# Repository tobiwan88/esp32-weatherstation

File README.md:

# esp32-weatherstation

Outdoor air-quality and weather stations for my own use (Munich): PM1 / PM2.5 / PM10, temperature, humidity and pressure, with an
optional ozone module, reported over WiFi to Home Assistant (MQTT). The AQI and trends are computed on the Home Assistant side.
Solar powered with optional USB, ESP32-S3, deep-sleep duty cycle (every 30 min; every 15 min only while USB or strong sun is
present). Custom PCBs assembled by JLCPCB. Some sites are sheltered with USB nearby, some are exposed on a roof or pole on solar
only; the design target is the exposed case.

**Status (2026-11-23):** the hardware is three boards plus bought parts. The power board and the main board have schematics,
placement and routing done and pass their checks (KiCad DRC clean, EMI rows OK); there are no fab files yet and nothing is ordered.
The sensor head board exists as an SHT45 design; the switch to the cheaper SHT40 decided in the requirements is not done yet.
Firmware is not started. Board by board: `hardware/README.md`.

## The system
| Part | What |
|---|---|
| Power board | BQ25798 charger fed from the solar panel (hardware MPPT) and USB, one 1S LiFePO4 26700 cell with protection IC, panel TVS and choke, cell fuse and NTC. 4 layers, at most 50 x 50 mm. No 3.3 V rail on this board |
| Main board | ESP32-S3-WROOM-1 module, USB-C (programming, debug, VBUS to the power board), 3.3 V buck-boost, switched 3V3_SW and 5V_SW rails, BMP580 pressure sensor, sensor ports (2 x Qwiic, 2.54 mm I2C header, 5 V UART, ozone module, rain/wind pulse port). 4 layers, at most 50 x 50 mm |
| Sensor head | temperature and humidity (Sensirion SHT4x) on its own small 2-layer board in a radiation shield, joined by a Qwiic cable |
| Bought | 5 W 6 V solar panel, LiFePO4 cell, PM sensor (DFRobot SEN0460 on I2C, or Plantower PMS7003 on UART), optional rain gauge, anemometer, ozone and UV modules, enclosure |
The power and main boards are joined by a keyed 2 x 10 header (J10: SYS, USB VBUS and D+/D-, charger I2C and interrupt, charge enable). A bought charger
module that supplies SYS can replace the power board. Contract and pin table: `hardware/ARCHITECTURE.md`.

## Numbers that drive the design
| | Value | Source |
|---|---|---|
| Budget | each JLCPCB assembly order under USD 100, whole project under USD 500 | `hardware/REQUIREMENTS-system.md` section 2 |
| Parts plus fees per order, 5 boards (before bare PCB, SMT joints, shipping) | power board USD 55.02, main board USD 88.91 (live stock and first price tier, 2026-11-24) | `hardware/calc/bom_check.py hardware/<board> --stock --qty 5` |
| Average current, 30 min cycle | 11.8 mA, 0.90 Wh/day | `hardware/calc/power_budget.py hardware/power-board` |
| Autonomy without sun | 11.1 days (at least 7 required) | same |
| Worst-month solar margin | 2.33 x (want 1.5 x) | same |
| Sleep current of the whole stack | 75 uA typical, 85 uA with datasheet maxima (target under 100 uA) | same |
The 15 min cycle draws 22 mA and gives 5.9 days, so it is allowed only with an external energy source. A real JLCPCB quote per
order is still needed: there is no scriptable quote.

## Where to look
- `hardware/README.md`: boards, status, and the map of the hardware tree. `hardware/PLAN.md`: what is done and what comes next.
- `hardware/REQUIREMENTS-system.md`, `hardware/ARCHITECTURE.md`, `hardware/DECISIONS.md`: requirements, how the boards fit, decisions.
- `hardware/GATES.md`: where each board stands in the six design gates.
- `firmware/`: ESP-IDF project (not started); the rules the hardware depends on are in `hardware/FIRMWARE-RULES.md`.
- `hw-kit/`: the reusable hardware kit (skills, agents, check scripts, templates) this project is built with; `CLAUDE.md`: agent notes.
- `scripts/check.sh`: the local gate (hardware checks, tests, privacy scan).

Built with the hardware kit in `hw-kit/`, which grew out of [desk_notifier](https://github.com/tobiwan88/desk_notifier). MIT license.

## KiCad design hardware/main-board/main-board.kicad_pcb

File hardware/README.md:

# Hardware: where to look

Boards (one folder each, profile in `board.yaml`, notes in `BOARD.md`). Gate output: `scripts/hw-check.sh`.

| Board | Role | State (details in its `BOARD.md`) |
|---|---|---|
| `power-board/` | charger, protection, solar and USB inputs, header to the main board | routed 2026-11-22, DRC 0 at all severities; no fab files yet |
| `main-board/` | MCU, 3.3 V and 5 V rails, USB-C, sensor ports | routed 2026-11-22, DRC clean (waived silk warnings listed there), EMI check OK; no fab files yet |
| `sht45-board/` | outdoor temperature and humidity head, Qwiic chain-out | layout done 2026-11-04: ERC 0, DRC 0 incl. warnings, parity clean |
| `bmp585-board/`, `veml6030-board/` | pressure and light add-ons on the same base | retired as ordered designs 2026-11-21; DRC clean, parity clean (2026-11-04) |
| `weatherstation-v1/` | first single-board design, kept as history: parts cards and datasheets (its fab files are local and gitignored) | superseded by the split |

| What | Where |
|---|---|
| System requirements, architecture, decisions that must not be lost | `REQUIREMENTS-system.md`, `ARCHITECTURE.md`, `DECISIONS.md` |
| Plan, review rounds, order notes | `PLAN.md`, `REVIEW-*.md`, `ORDER-sensor-boards.md`, `<board>/ORDER.md` |
| Board profile files read by the scripts | `<board>/board.yaml`, `critical.yaml`, `emi.yaml`, `parts/` |
| Board-neutral checks, tools, fab rules | `calc/`, `tools/`, `rules/` (installed from `../hw-kit/tooling`) |
| Generators and project build scripts | `gen/`, `tools/build_*.sh`, `tools/route_*.sh` |
| Skills and agents | `../.claude/` (installed from `../hw-kit`; read `hw-base` first) |
| Earlier project's pipeline to copy from | `reference/desk_notifier/` |

New board: `scripts/new-board.sh <name>`. The kit and how to reuse it in another project: `../hw-kit/README.md`.

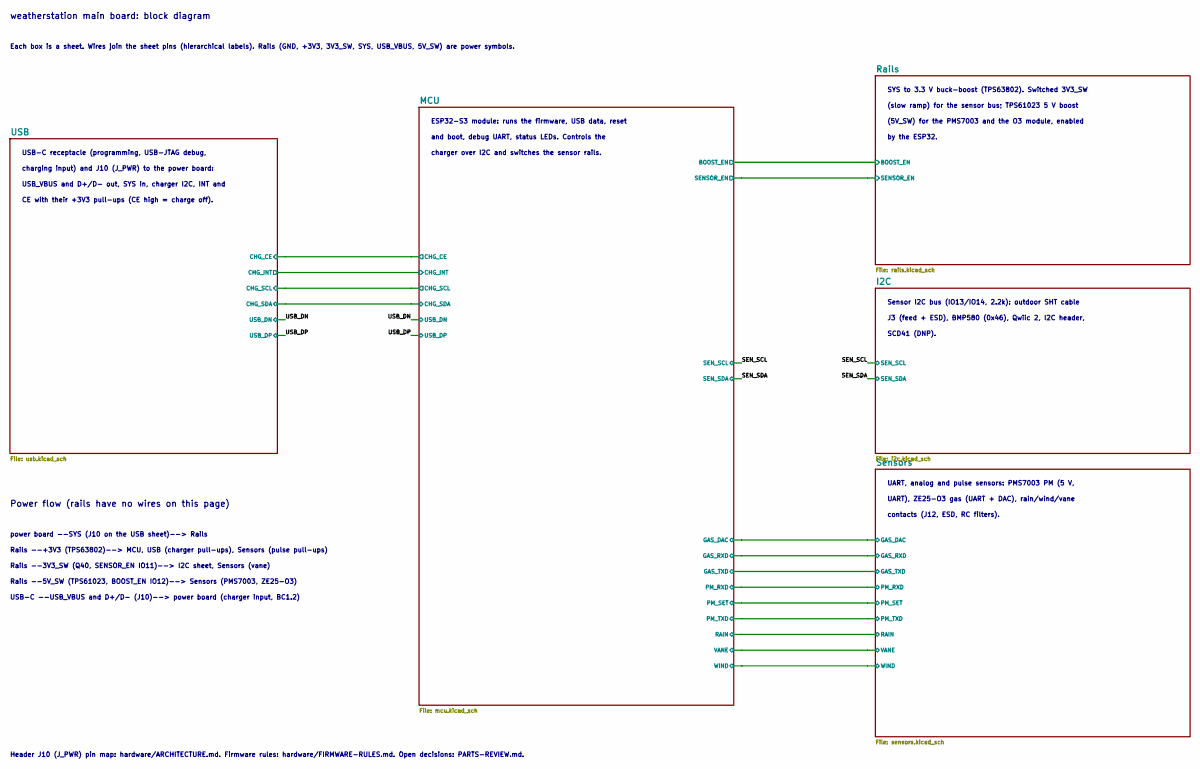
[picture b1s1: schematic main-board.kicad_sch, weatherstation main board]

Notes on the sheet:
weatherstation main board: block diagram
Each box is a sheet. Wires join the sheet pins (hierarchical labels). Rails (GND, +3V3, 3V3_SW, SYS, USB_VBUS, 5V_SW) are power symbols.
Power flow (rails have no wires on this page)
power board --SYS (J10 on the USB sheet)--> Rails
Rails --+3V3 (TPS63802)--> MCU, USB (charger pull-ups), Sensors (pulse pull-ups)
Rails --3V3_SW (Q40, SENSOR_EN IO11)--> I2C sheet, Sensors (vane)
Rails --5V_SW (TPS61023, BOOST_EN IO12)--> Sensors (PMS7003, ZE25-O3)
USB-C --USB_VBUS and D+/D- (J10)--> power board (charger input, BC1.2)
Header J10 (J_PWR) pin map: hardware/ARCHITECTURE.md. Firmware rules: hardware/FIRMWARE-RULES.md. Open decisions: PARTS-REVIEW.md.
USB-C receptacle (programming, USB-JTAG debug,
charging input) and J10 (J_PWR) to the power board:
USB_VBUS and D+/D- out, SYS in, charger I2C, INT and
CE with their +3V3 pull-ups (CE high = charge off).
ESP32-S3 module: runs the firmware, USB data, reset
and boot, debug UART, status LEDs. Controls the
charger over I2C and switches the sensor rails.
SYS to 3.3 V buck-boost (TPS63802). Switched 3V3_SW
(slow ramp) for the sensor bus; TPS61023 5 V boost
(5V_SW) for the PMS7003 and the O3 module, enabled
by the ESP32.
Sensor I2C bus (IO13/IO14, 2.2k): outdoor SHT cable
J3 (feed + ESD), BMP580 (0x46), Qwiic 2, I2C header,
SCD41 (DNP).
UART, analog and pulse sensors: PMS7003 PM (5 V,
UART), ZE25-O3 gas (UART + DAC), rain/wind/vane
contacts (J12, ESD, RC filters).

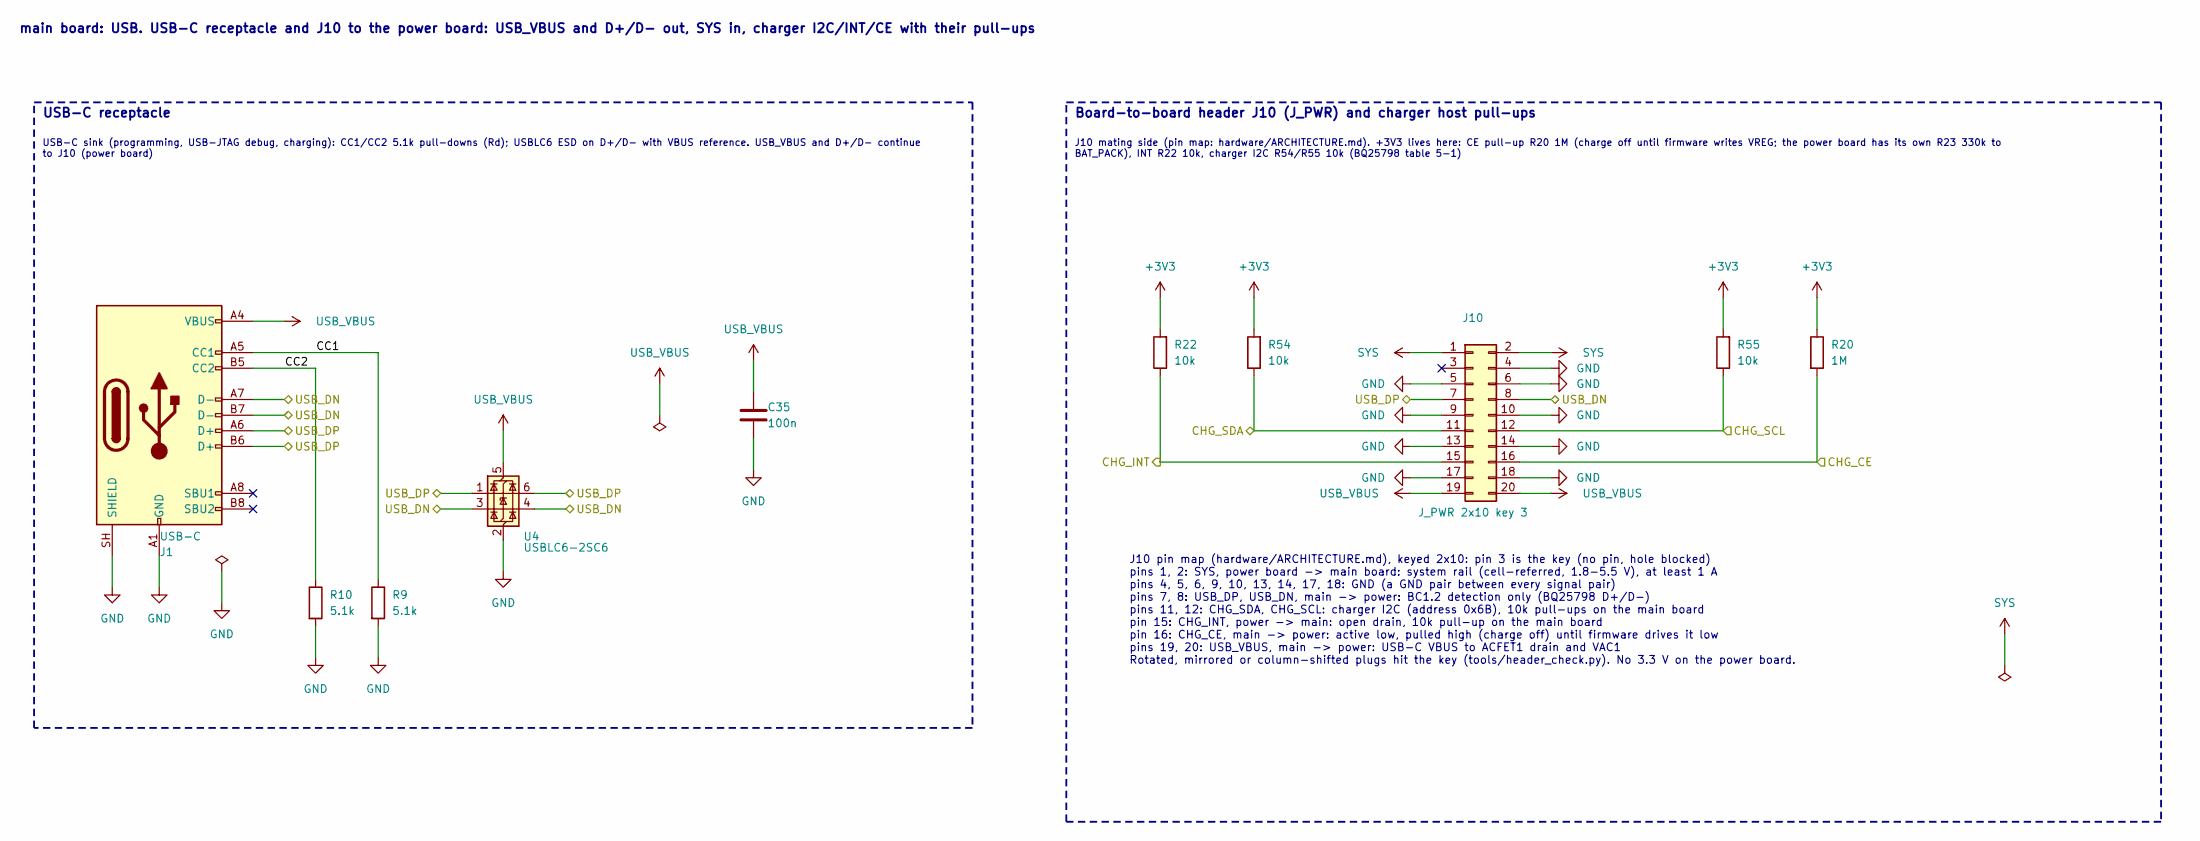
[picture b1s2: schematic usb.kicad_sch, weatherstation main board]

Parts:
C35: 100n; C_0402_1005Metric; LCSC C307331
J1: USB-C; USB_C_Receptacle_HRO_TYPE-C-31-M-12; LCSC C165948
J10: J_PWR 2x10 key 3; PinHeader_2x10_P2.54mm_Vertical
R9, R10: 5.1k; R_0402_1005Metric; LCSC C25905
R20: 1M; R_0402_1005Metric; LCSC C26083
R22, R54, R55: 10k; R_0402_1005Metric; LCSC C25744
U4: USBLC6-2SC6; SOT-23-6; LCSC C7519

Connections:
+3V3: R20.1, R22.2, R54.2, R55.2; also elsewhere on the board
/MCU/CHG_CE: J10.16, R20.2; also elsewhere on the board
/MCU/CHG_INT: J10.15, R22.1; also elsewhere on the board
/MCU/CHG_SCL: J10.12, R55.1; also elsewhere on the board
/MCU/CHG_SDA: J10.11, R54.1; also elsewhere on the board
/USB/CC1: J1.A5 (CC1), R9.1
/USB/CC2: J1.B5 (CC2), R10.1
/USB_DN: J1.A7 (D-), J1.B7 (D-), J10.8, U4.3 (I/O2), U4.4 (I/O2); also elsewhere on the board
/USB_DP: J1.A6 (D+), J1.B6 (D+), J10.7, U4.1 (I/O1), U4.6 (I/O1); also elsewhere on the board
GND: C35.2, J1.A1 (GND), J1.A12 (GND), J1.B1 (GND), J1.B12 (GND), J1.SH (SHIELD), J10.4, J10.5, J10.6, J10.9, J10.10, J10.13, J10.14, J10.17, J10.18, R9.2, R10.2, U4.2 (GND); also elsewhere on the board
SYS: J10.1, J10.2; also elsewhere on the board
USB_VBUS: C35.1, J1.A4 (VBUS), J1.A9 (VBUS), J1.B4 (VBUS), J1.B9 (VBUS), J10.19, J10.20, U4.5 (VBUS)

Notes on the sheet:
USB-C receptacle
USB-C sink (programming, USB-JTAG debug, charging): CC1/CC2 5.1k pull-downs (Rd); USBLC6 ESD on D+/D- with VBUS reference. USB_VBUS and D+/D- continue to J10 (power board)
Board-to-board header J10 (J_PWR) and charger host pull-ups
J10 mating side (pin map: hardware/ARCHITECTURE.md). +3V3 lives here: CE pull-up R20 1M (charge off until firmware writes VREG; the power board has its own R23 330k to BAT_PACK), INT R22 10k, charger I2C R54/R55 10k (BQ25798 table 5-1)
J10 pin map (hardware/ARCHITECTURE.md), keyed 2x10: pin 3 is the key (no pin, hole blocked) pins 1, 2: SYS, power board -> main board: system rail (cell-referred, 1.8-5.5 V), at least 1 A pins 4, 5, 6, 9, 10, 13, 14, 17, 18: GND (a GND pair between every signal pair) pins 7, 8: USB_DP, USB_DN, main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
main board: USB. USB-C receptacle and J10 to the power board: USB_VBUS and D+/D- out, SYS in, charger I2C/INT/CE with their pull-ups

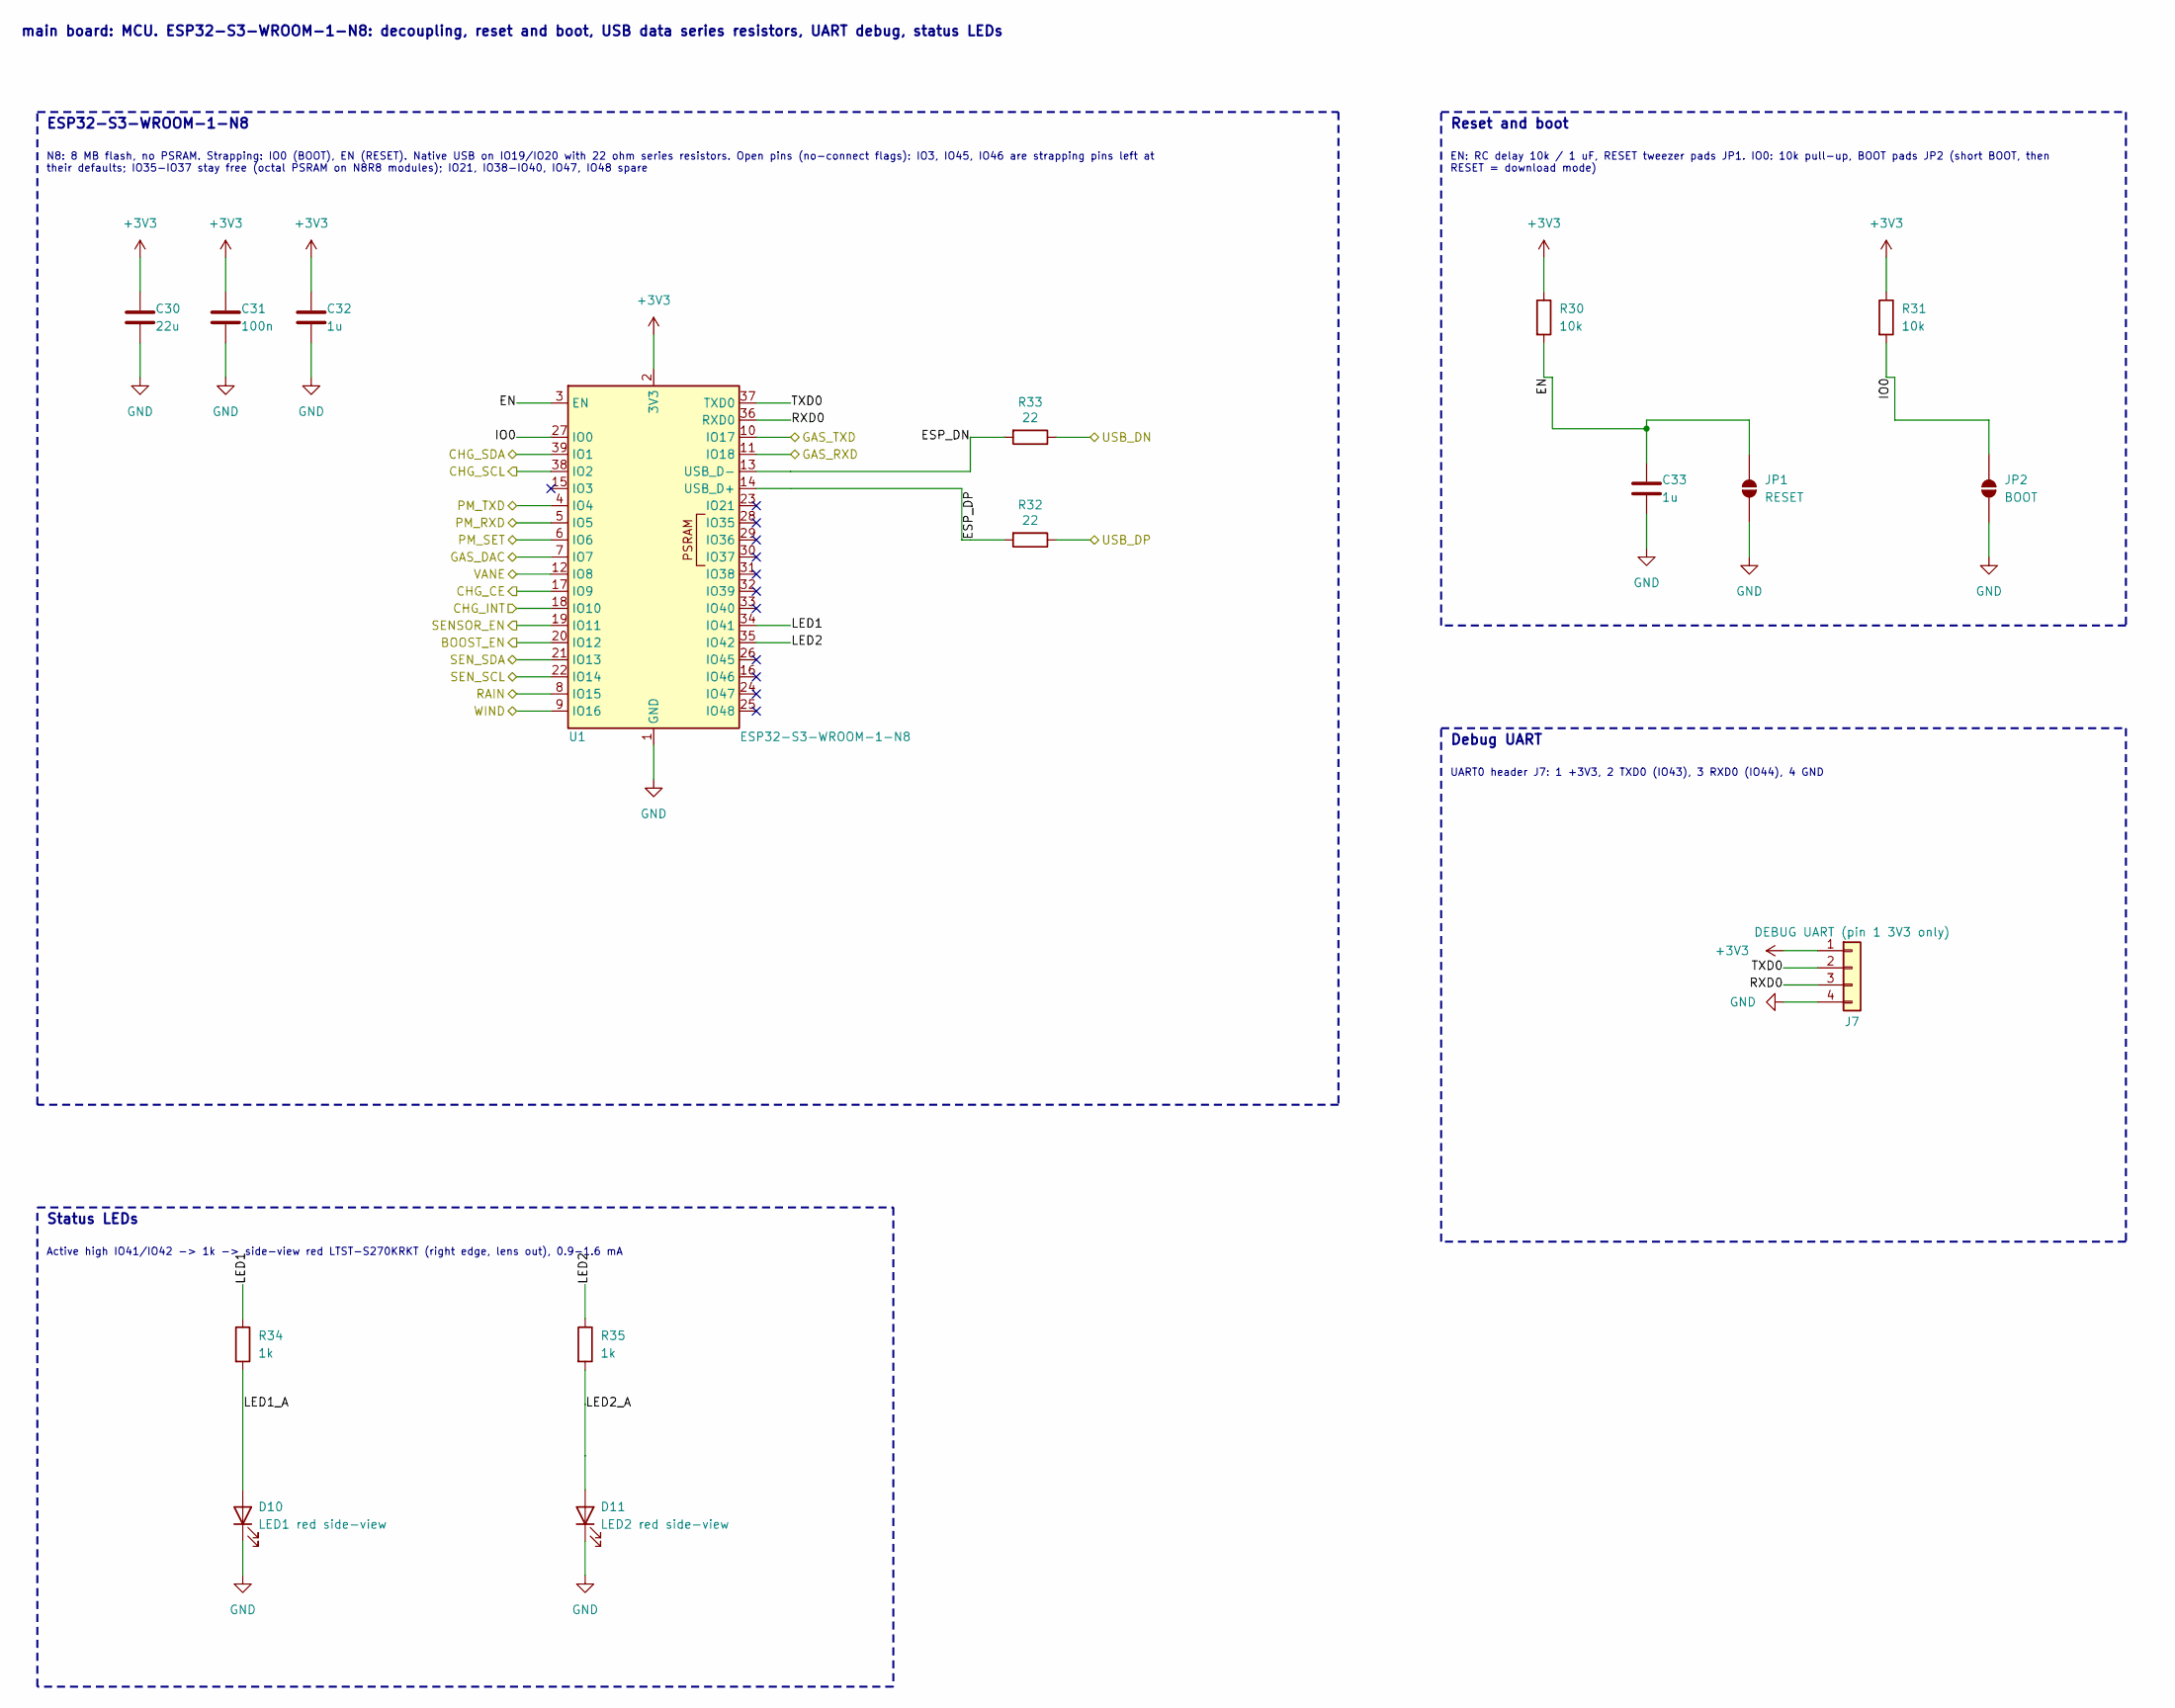
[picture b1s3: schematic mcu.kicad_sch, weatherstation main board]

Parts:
C30: 22u; C_0805_2012Metric; LCSC C45783
C31: 100n; C_0402_1005Metric; LCSC C307331
C32, C33: 1u; C_0402_1005Metric; LCSC C52923
D10: LED1 red side-view; LED_LiteOn_LTST-S270_SideView; LCSC C125114
D11: LED2 red side-view; LED_LiteOn_LTST-S270_SideView; LCSC C125114
J7: DEBUG UART (pin 1 3V3 only); PinHeader_1x04_P2.54mm_Vertical
JP1: RESET; SolderJumper-2_P1.3mm_Open_RoundedPad1.0x1.5mm
JP2: BOOT; SolderJumper-2_P1.3mm_Open_RoundedPad1.0x1.5mm
R30, R31: 10k; R_0402_1005Metric; LCSC C25744
R32, R33: 22; R_0402_1005Metric; LCSC C25092
R34, R35: 1k; R_0402_1005Metric; LCSC C11702
U1: ESP32-S3-WROOM-1-N8; ESP32-S3-WROOM-1; LCSC C2913198

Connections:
+3V3: C30.1, C31.1, C32.1, J7.1, R30.1, R31.1, U1.2 (3V3); also elsewhere on the board
/MCU/BOOST_EN: U1.20 (IO12); also elsewhere on the board
/MCU/CHG_CE: U1.17 (IO9); also elsewhere on the board
/MCU/CHG_INT: U1.18 (IO10); also elsewhere on the board
/MCU/CHG_SCL: U1.38 (IO2); also elsewhere on the board
/MCU/CHG_SDA: U1.39 (IO1); also elsewhere on the board
/MCU/EN: C33.1, JP1.1 (A), R30.2, U1.3 (EN)
/MCU/ESP_DN: R33.2, U1.13 (USB_D-)
/MCU/ESP_DP: R32.2, U1.14 (USB_D+)
/MCU/GAS_DAC: U1.7 (IO7); also elsewhere on the board
/MCU/GAS_RXD: U1.11 (IO18); also elsewhere on the board
/MCU/GAS_TXD: U1.10 (IO17); also elsewhere on the board
/MCU/IO0: JP2.1 (A), R31.2, U1.27 (IO0)
/MCU/LED1: R34.1, U1.34 (IO41)
/MCU/LED1_A: D10.2 (A), R34.2
/MCU/LED2: R35.1, U1.35 (IO42)
/MCU/LED2_A: D11.2 (A), R35.2
/MCU/PM_RXD: U1.5 (IO5); also elsewhere on the board
/MCU/PM_SET: U1.6 (IO6); also elsewhere on the board
/MCU/PM_TXD: U1.4 (IO4); also elsewhere on the board
/MCU/RAIN: U1.8 (IO15); also elsewhere on the board
/MCU/RXD0: J7.3, U1.36 (RXD0)
/MCU/SENSOR_EN: U1.19 (IO11); also elsewhere on the board
/MCU/TXD0: J7.2, U1.37 (TXD0)
/MCU/VANE: U1.12 (IO8); also elsewhere on the board
/MCU/WIND: U1.9 (IO16); also elsewhere on the board
/SEN_SCL: U1.22 (IO14); also elsewhere on the board
/SEN_SDA: U1.21 (IO13); also elsewhere on the board
/USB_DN: R33.1; also elsewhere on the board
/USB_DP: R32.1; also elsewhere on the board
GND: C30.2, C31.2, C32.2, C33.2, D10.1 (K), D11.1 (K), J7.4, JP1.2 (B), JP2.2 (B), U1.1 (GND), U1.40 (GND), U1.41 (GND); also elsewhere on the board

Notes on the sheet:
ESP32-S3-WROOM-1-N8
N8: 8 MB flash, no PSRAM. Strapping: IO0 (BOOT), EN (RESET). Native USB on IO19/IO20 with 22 ohm series resistors. Open pins (no-connect flags): IO3, IO45, IO46 are strapping pins left at their defaults; IO35-IO37 stay free (octal PSRAM on N8R8 modules); IO21, IO38-IO40, IO47, IO48 spare
Reset and boot
EN: RC delay 10k / 1 uF, RESET tweezer pads JP1. IO0: 10k pull-up, BOOT pads JP2 (short BOOT, then RESET = download mode)
Debug UART
UART0 header J7: 1 +3V3, 2 TXD0 (IO43), 3 RXD0 (IO44), 4 GND
Status LEDs
Active high IO41/IO42 -> 1k -> side-view red LTST-S270KRKT (right edge, lens out), 0.9-1.6 mA
main board: MCU. ESP32-S3-WROOM-1-N8: decoupling, reset and boot, USB data series resistors, UART debug, status LEDs

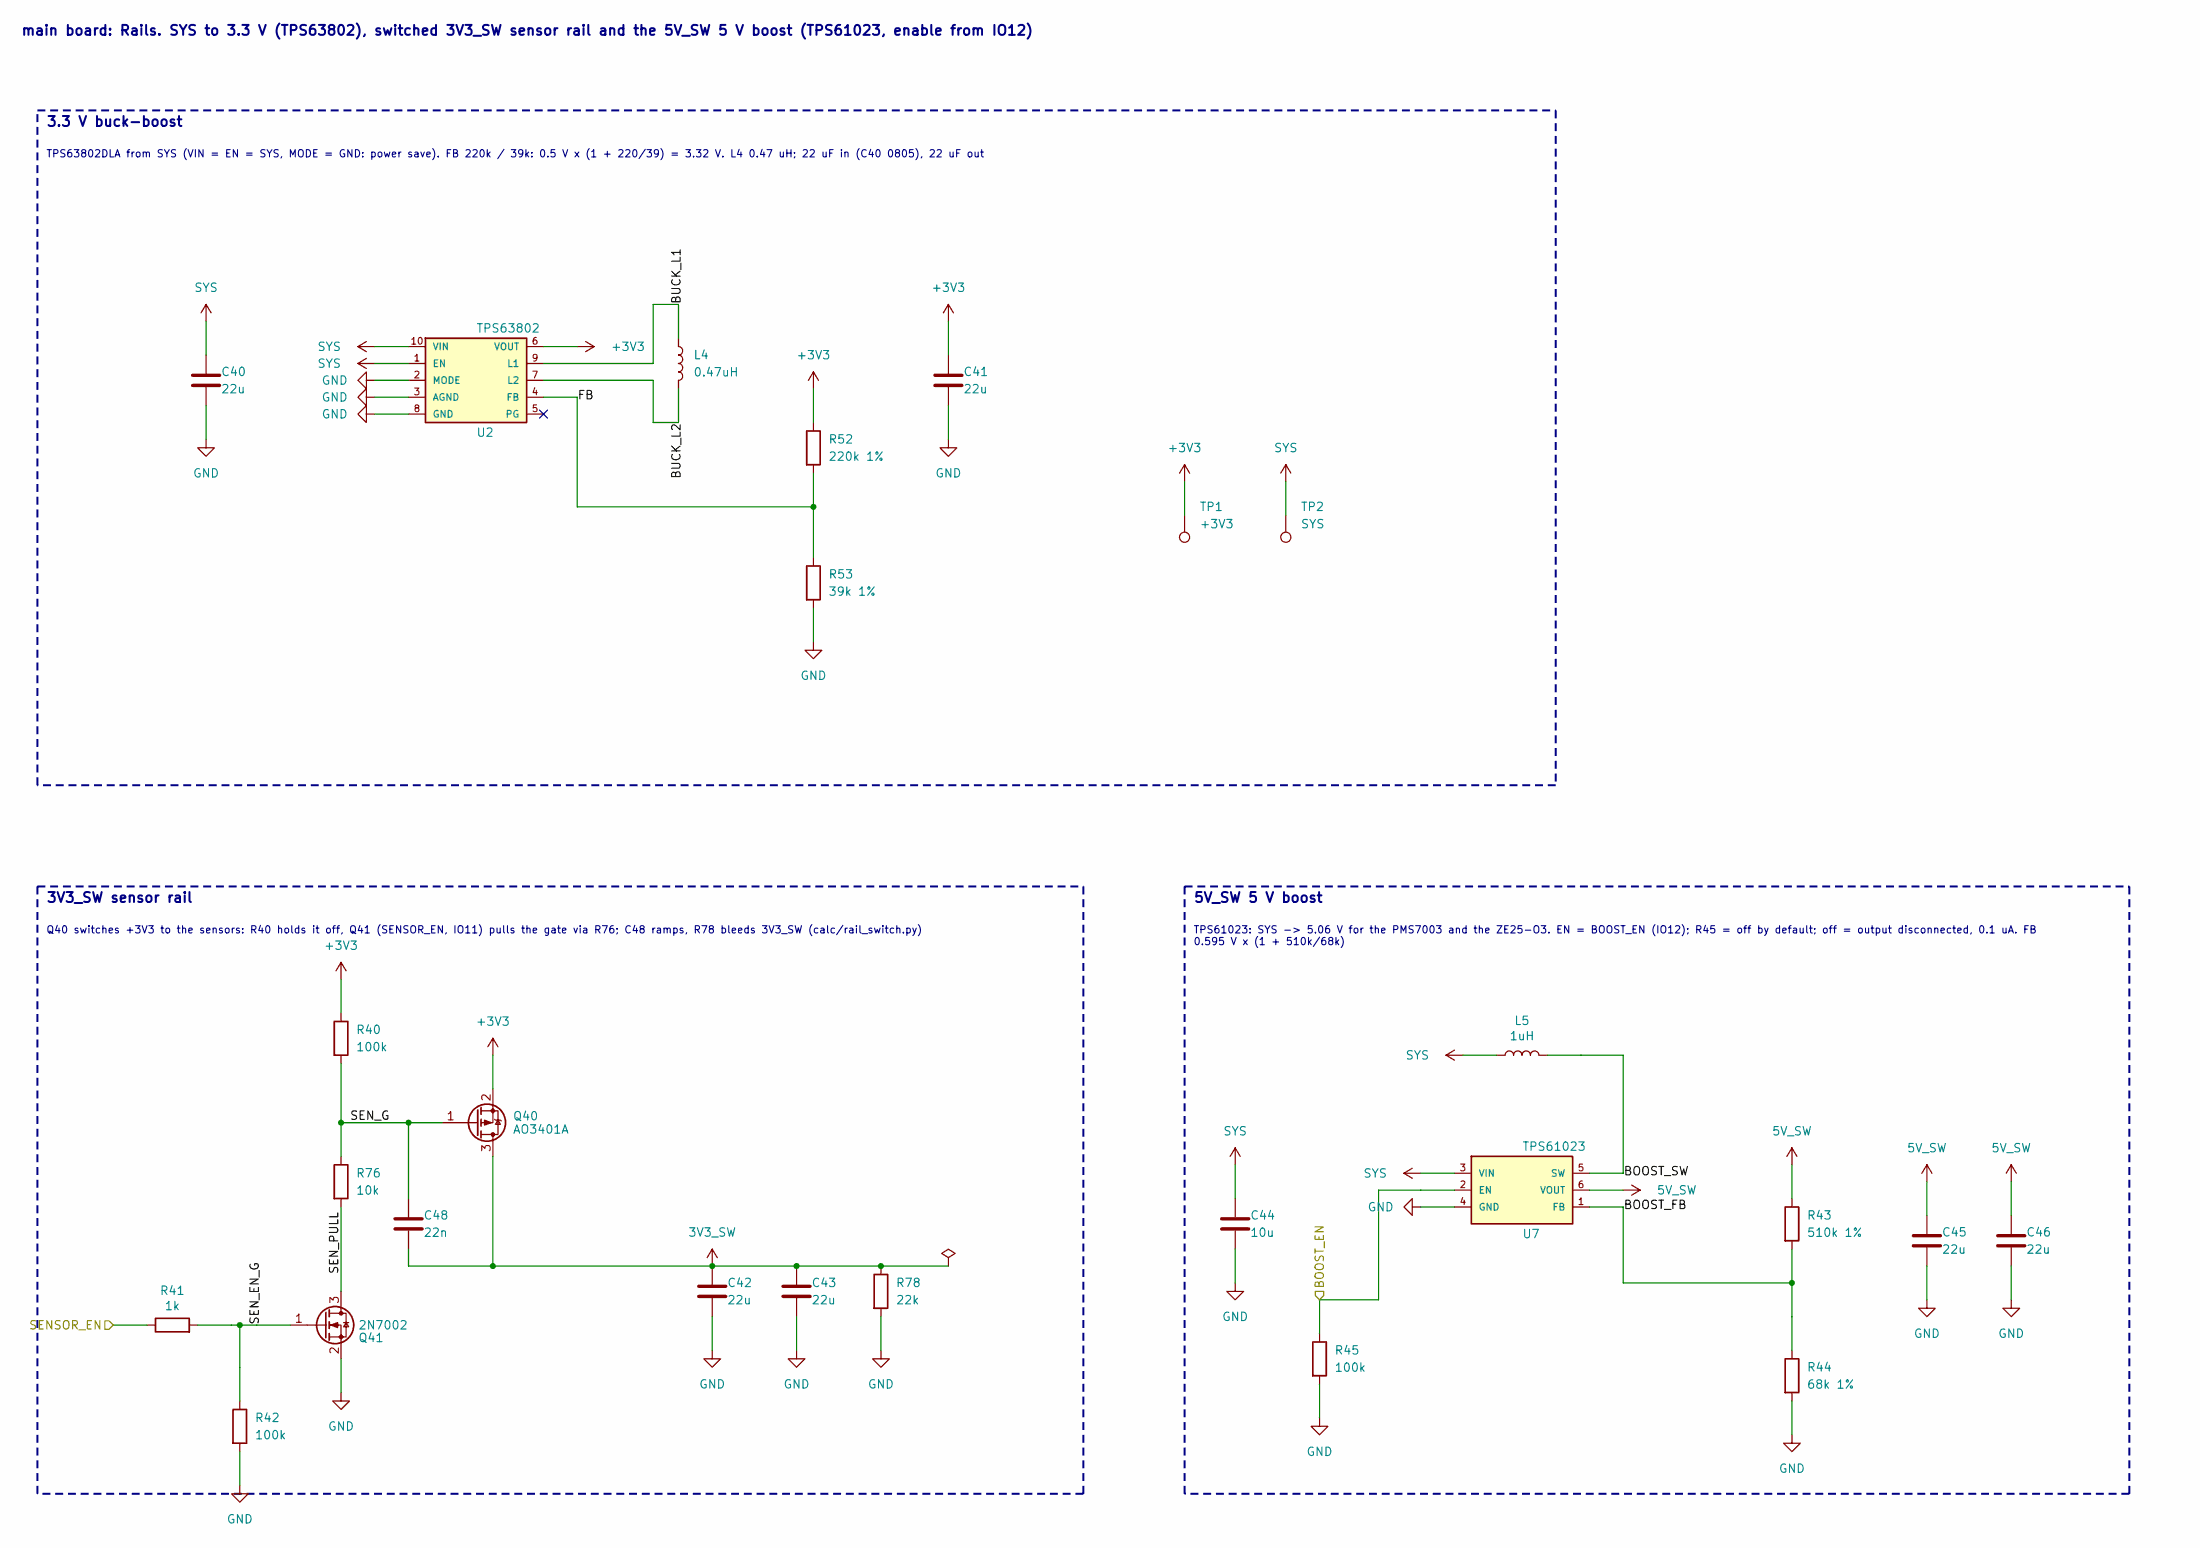
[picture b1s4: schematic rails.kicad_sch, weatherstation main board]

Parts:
C40, C41, C42, C43, C45, C46: 22u; C_0805_2012Metric; LCSC C45783
C44: 10u; C_0603_1608Metric; LCSC C19702
C48: 22n; C_0402_1005Metric; LCSC C1532
L4: 0.47uH; L_Sunlord_WPN201610H; LCSC C97009
L5: 1uH; L_TDK_VLS252010; LCSC C88211
Q40: AO3401A; SOT-23; LCSC C15127
Q41: 2N7002; SOT-23; LCSC C8545
R40, R42, R45: 100k; R_0402_1005Metric; LCSC C25741
R41: 1k; R_0402_1005Metric; LCSC C11702
R43: 510k 1%; R_0603_1608Metric; LCSC C23192
R44: 68k 1%; R_0603_1608Metric; LCSC C23231
R52: 220k 1%; R_0603_1608Metric; LCSC C22961
R53: 39k 1%; R_0603_1608Metric; LCSC C23153
R76: 10k; R_0402_1005Metric; LCSC C25744
R78: 22k; R_0402_1005Metric; LCSC C25768
TP1: +3V3; TestPoint_Pad_D1.5mm
TP2: SYS; TestPoint_Pad_D1.5mm
U2: TPS63802; TPS63802_DLA_VSON-HR-10_2x3mm; LCSC C2845237
U7: TPS61023; SOT-563; LCSC C919459

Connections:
3V3_SW: C42.1, C43.1, C48.2, Q40.3 (D), R78.1; also elsewhere on the board
5V_SW: C45.1, C46.1, R43.1, U7.6 (VOUT); also elsewhere on the board
+3V3: C41.1, Q40.2 (S), R40.1, R52.1, TP1.1, U2.6 (VOUT); also elsewhere on the board
/MCU/BOOST_EN: R45.1, U7.2 (EN); also elsewhere on the board
/MCU/SENSOR_EN: R41.1; also elsewhere on the board
/Rails/BOOST_FB: R43.2, R44.1, U7.1 (FB)
/Rails/BOOST_SW: L5.2, U7.5 (SW)
/Rails/BUCK_L1: L4.1, U2.9 (L1)
/Rails/BUCK_L2: L4.2, U2.7 (L2)
/Rails/FB: R52.2, R53.1, U2.4 (FB)
/Rails/SEN_EN_G: Q41.1 (G), R41.2, R42.1
/Rails/SEN_G: C48.1, Q40.1 (G), R40.2, R76.1
/Rails/SEN_PULL: Q41.3 (D), R76.2
GND: C40.2, C41.2, C42.2, C43.2, C44.2, C45.2, C46.2, Q41.2 (S), R42.2, R44.2, R45.2, R53.2, R78.2, U2.2 (MODE), U2.3 (AGND), U2.8 (GND), U7.4 (GND); also elsewhere on the board
SYS: C40.1, C44.1, L5.1, TP2.1, U2.1 (EN), U2.10 (VIN), U7.3 (VIN); also elsewhere on the board

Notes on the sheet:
3.3 V buck-boost
TPS63802DLA from SYS (VIN = EN = SYS, MODE = GND: power save). FB 220k / 39k: 0.5 V x (1 + 220/39) = 3.32 V. L4 0.47 uH; 22 uF in (C40 0805), 22 uF out
3V3_SW sensor rail
Q40 switches +3V3 to the sensors: R40 holds it off, Q41 (SENSOR_EN, IO11) pulls the gate via R76; C48 ramps, R78 bleeds 3V3_SW (calc/rail_switch.py)
5V_SW 5 V boost
TPS61023: SYS -> 5.06 V for the PMS7003 and the ZE25-O3. EN = BOOST_EN (IO12); R45 = off by default; off = output disconnected, 0.1 uA. FB 0.595 V x (1 + 510k/68k)
main board: Rails. SYS to 3.3 V (TPS63802), switched 3V3_SW sensor rail and the 5V_SW 5 V boost (TPS61023, enable from IO12)

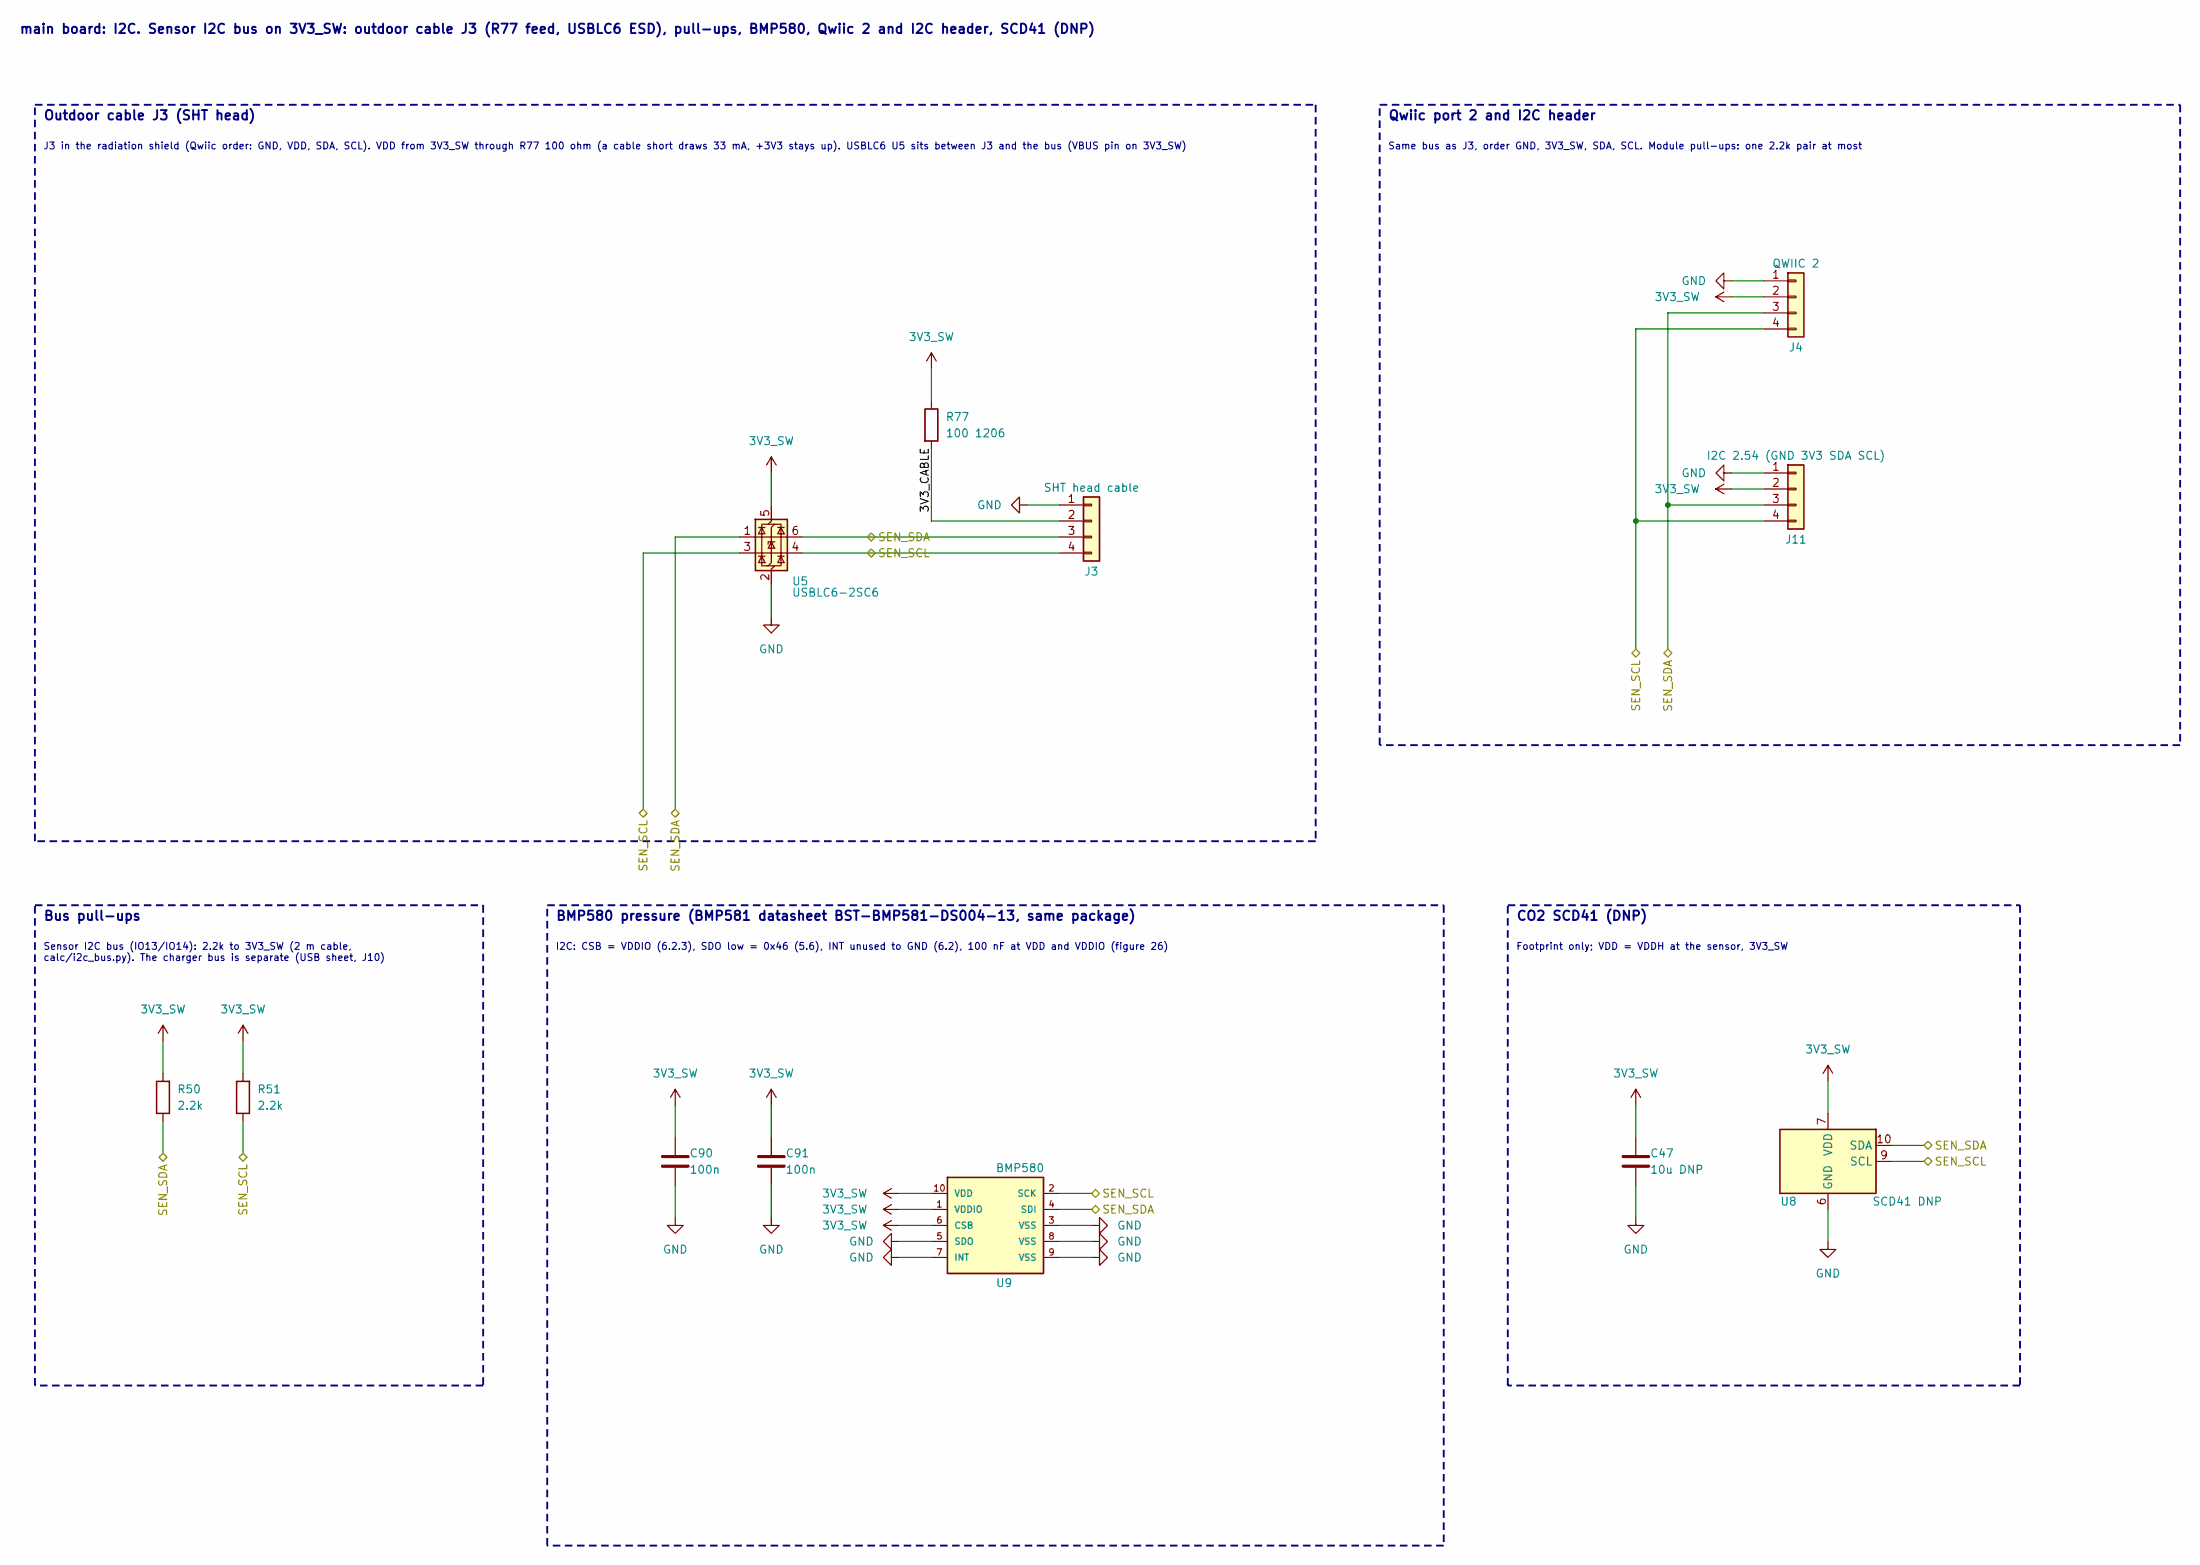
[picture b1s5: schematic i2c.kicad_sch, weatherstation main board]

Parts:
C47: 10u DNP; C_0603_1608Metric
C90, C91: 100n; C_0402_1005Metric; LCSC C307331
J3: SHT head cable; JST_SH_SM04B-SRSS-TB_1x04-1MP_P1.00mm_Horizontal; LCSC C160404
J4: QWIIC 2; JST_SH_SM04B-SRSS-TB_1x04-1MP_P1.00mm_Horizontal; LCSC C160404
J11: I2C 2.54 (GND 3V3 SDA SCL); PinHeader_1x04_P2.54mm_Vertical
R50, R51: 2.2k; R_0402_1005Metric; LCSC C25879
R77: 100 1206; R_1206_3216Metric; LCSC C17901
U5: USBLC6-2SC6; SOT-23-6; LCSC C7519
U8: SCD41 DNP; Sensirion_SCD4x-1EP_10.1x10.1mm_P1.25mm_EP4.8x4.8mm
U9: BMP580; Bosch_LGA-10_2x2mm; LCSC C22391138

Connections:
3V3_SW: C47.1, C90.1, C91.1, J4.2, J11.2, R50.2, R51.2, R77.1, U5.5 (VBUS), U8.7 (VDD), U8.19 (VDD), U9.1 (VDDIO), U9.6 (CSB), U9.10 (VDD); also elsewhere on the board
/I2C/3V3_CABLE: J3.2, R77.2
/SEN_SCL: J3.4, J4.4, J11.4, R51.1, U5.3 (I/O2), U5.4 (I/O2), U8.9 (SCL), U9.2 (SCK); also elsewhere on the board
/SEN_SDA: J3.3, J4.3, J11.3, R50.1, U5.1 (I/O1), U5.6 (I/O1), U8.10 (SDA), U9.4 (SDI); also elsewhere on the board
GND: C47.2, C90.2, C91.2, J3.1, J4.1, J11.1, U5.2 (GND), U8.6 (GND), U8.20 (GND), U8.21 (GND), U9.3 (VSS), U9.5 (SDO), U9.7 (INT), U9.8 (VSS), U9.9 (VSS); also elsewhere on the board

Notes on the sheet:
Outdoor cable J3 (SHT head)
J3 in the radiation shield (Qwiic order: GND, VDD, SDA, SCL). VDD from 3V3_SW through R77 100 ohm (a cable short draws 33 mA, +3V3 stays up). USBLC6 U5 sits between J3 and the bus (VBUS pin on 3V3_SW)
Qwiic port 2 and I2C header
Same bus as J3, order GND, 3V3_SW, SDA, SCL. Module pull-ups: one 2.2k pair at most
Bus pull-ups
Sensor I2C bus (IO13/IO14): 2.2k to 3V3_SW (2 m cable, calc/i2c_bus.py). The charger bus is separate (USB sheet, J10)
BMP580 pressure (BMP581 datasheet BST-BMP581-DS004-13, same package)
I2C: CSB = VDDIO (6.2.3), SDO low = 0x46 (5.6), INT unused to GND (6.2), 100 nF at VDD and VDDIO (figure 26)
CO2 SCD41 (DNP)
Footprint only; VDD = VDDH at the sensor, 3V3_SW
main board: I2C. Sensor I2C bus on 3V3_SW: outdoor cable J3 (R77 feed, USBLC6 ESD), pull-ups, BMP580, Qwiic 2 and I2C header, SCD41 (DNP)
